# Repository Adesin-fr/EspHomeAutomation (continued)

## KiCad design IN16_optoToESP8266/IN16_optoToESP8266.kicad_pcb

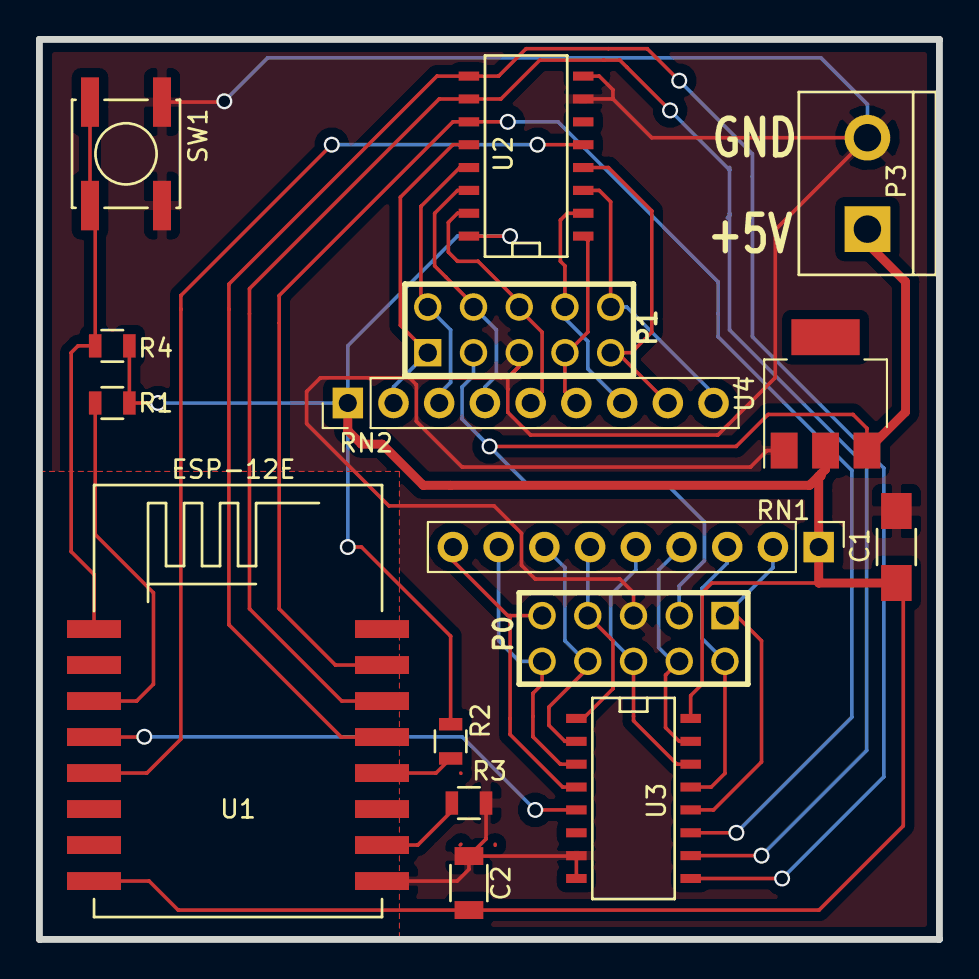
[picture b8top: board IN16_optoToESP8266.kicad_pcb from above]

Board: 2 copper layers, 50.0 x 50.0 mm, 16 parts (0 on the bottom side), 28 nets.

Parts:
C1: 10uF; R_1206_HandSoldering
C2: 100nF; C_1206
P0, P1: CONN_10; PIN_ARRAY_5x2
P3: 5VIN; bornier2
R1, R2, R3, R4: 10k; R_0805
RN1, RN2: RN10K; Pin_Header_Straight_1x09_Pitch2.54mm
SW1: Switch_DPST; SW_SPST_EVPBF
U1: ESP-12E; ESP-12
U2, U3: 74HC151; SO-16-N
U4: AMS1117; SOT-223

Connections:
/5VIN: P0.3, P1.3, P3.1, U4.3
/IN0: P1.1, RN2.2, U2.12
/IN1: P1.2, RN2.3, U2.13
/IN2: P1.4, RN2.4, U2.14
/IN3: P1.6, RN2.5, U2.15
/IN4: P1.7, RN2.6, U2.1
/IN5: P1.8, RN2.7, U2.2
/IN6: P1.9, RN2.8, U2.4
/IN7: P1.10, RN2.9, U2.3
/IN8: P0.1, RN1.2, U3.12
/IN9: P0.2, RN1.3, U3.13
/IN10: P0.4, RN1.4, U3.15
/IN11: P0.6, RN1.5, U3.14
/IN12: P0.7, RN1.6, U3.1
/IN13: P0.8, RN1.7, U3.2
/IN14: P0.9, RN1.9, U3.4
/IN15: P0.10, RN1.8, U3.3
/MUX1: U1.4, U3.5
/MUX2: U1.5, U2.5
/MUXA: U1.15, U2.11, U3.11
/MUXB: U1.14, U2.10, U3.10
/MUXC: U1.13, U2.9, U3.9
/RST: R4.1, SW1.2, U1.1
unnamed: R1.1, U1.3
unnamed: R2.2, U1.12
unnamed: R3.1, U1.10
VCC: C1.1, C2.1, R1.2, R2.1, R4.2, RN1.1, RN2.1, U1.8, U2.16, U3.16, U4.2
VSS: C1.2, C2.2, P0.5, P1.5, P3.2, R3.2, SW1.1, U1.9, U2.7, U3.7, U4.1

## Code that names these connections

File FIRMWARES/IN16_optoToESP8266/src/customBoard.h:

#ifndef customBoard_h
#define customBoard_h

#include "baseBoard.h"

// Board specific defines :

      #define SUBNODECOUNT    16       // how many sub-nodes should we present
      #define SHORTPULSE      60		         // Temps pour un appui court en ms
      #define LONGPULSE       500		         // Temps pour un appui long en ms

      #define PIN_MUX1    16
      #define PIN_MUX2    14
      #define MUXA	      3
      #define MUXB	      5
      #define MUXC	      4

      #define BUTTON_STATUS_NONE 0
      #define BUTTON_STATUS_PULSE_BEGIN 1
      #define BUTTON_STATUS_PULSE_END 2
      #define BUTTON_STATUS_HOLD_BEGIN 3
      #define BUTTON_STATUS_HOLD_END 4

// Board specific variables :

      extern      unsigned long previousTime ;
      extern      unsigned long pushTime[SUBNODECOUNT];
      extern      byte pushState[SUBNODECOUNT];
      extern      byte justPushed[SUBNODECOUNT];
      extern      byte justReleasedShortPush[SUBNODECOUNT];
      extern      byte justLongPushed[SUBNODECOUNT];
      extern      byte justReleasedLongPushed[SUBNODECOUNT];
      extern      String lastEvents;




      /*  Board specific MANDATORY functions :
          These functions must be implemented :
              void boardSetup()
              void boardLoop()
              void mqttSendHassDiscovery()    // if HASS_AUTODISCOVERY defined
              void handleBoardSettings()
      */

            void boardSetup();
            void boardLoop();
            void handleBoardSettings();
            void mqttSendHassDiscovery();
            void handleMqttIncomingMessage(String topic, String payload);

    // Board specific custom functions :

            boolean lirePin(byte numPin);
            void SendSensorStatus(byte numpin, byte actionType);
            void checkPushes();
            void handleDelInRule();
            void handleInputSettings();
            void handleClearAllRules();


#endif

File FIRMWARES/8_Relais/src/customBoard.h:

#ifndef customBoard_h
#define customBoard_h

#include "baseBoard.h"

// Board specific defines :

      #define SUBNODECOUNT    7       // how many sub-nodes should we present

      #define PIN_SRCLK    12
      #define PIN_SER      13
      #define PIN_RCLK     14

      #define ON_VALUE      1
      #define OFF_VALUE     0

// Board specific variables :

      extern      unsigned long previousTime ;
      extern      byte outputState;
      extern      String lastEvents;
      extern      int outputTimer[SUBNODECOUNT];    // Timer in SECONDS for each output
      extern      unsigned long outputStartedMillis[SUBNODECOUNT];    // Timer in SECONDS for each output

/*  Board specific MANDATORY functions :
    These functions must be implemented :
      void boardSetup()
      void boardLoop()
      void mqttSendHassDiscovery()    // if HASS_AUTODISCOVERY defined
      void handleBoardSettings()
*/

            void boardSetup();
            void boardLoop();
            void handleBoardSettings();
            void mqttSendHassDiscovery();
            void handleMqttIncomingMessage(String myTopic, String sPayload);

      // Board specific custom functions :

            void setOutput(byte numPin, boolean newValue);
            void reportOutputState(byte numPin);
            void flushOutput();


#endif

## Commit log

2019-03-05 Updated IN16 Firmware Added firmware copy post-build script Added binary file
2019-03-05 Finished FilPilote schematic + PCB
2019-03-05 Moved all kicad projects into the Hardware folder
2019-03-05 Modified 8_FilPilote Firmware
2019-03-06 - Modified almost all hardware boards : They were missing a pull-up resistor on GPIO2, which made impossible to flash. - Updated baseBoard.* files
2019-03-06 fixed the 8_Relais Firmware and the 8_FilPilote
2019-03-07 Updates to 4_Volets firmware
2019-03-07 Added Sketchup file for enclosures
2019-03-07 Added STL files for enclosures
2019-03-14 Fix on the BaseBoard class
2019-03-14 Fix auto reset issue on wifi disconnect (wait 10 seconds before giving up and reseting)
2019-03-14 First stable version of 1_Volet
2019-12-03 New version of IN16 ESP8266
